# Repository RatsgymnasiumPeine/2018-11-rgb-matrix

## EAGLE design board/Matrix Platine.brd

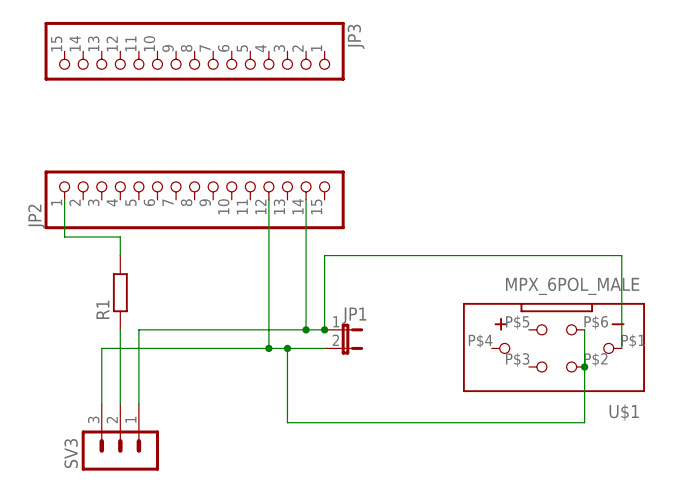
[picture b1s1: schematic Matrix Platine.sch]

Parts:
JP1: JP1E; JP1
JP2, JP3: PINHD-1X15; 1X15
R1: R-EU_0204/7; 0204/7
SV3: MA03-1
U$1: MPX_6POL_MALE; MPX_MALE

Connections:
unnamed: JP2.1, R1.2
unnamed: JP1.1, JP2.14, SV3.1, U$1.P$1 (1)
unnamed: JP1.2, JP2.12, SV3.3, U$1.P$2 (2), U$1.P$6 (6)
unnamed: R1.1, SV3.2

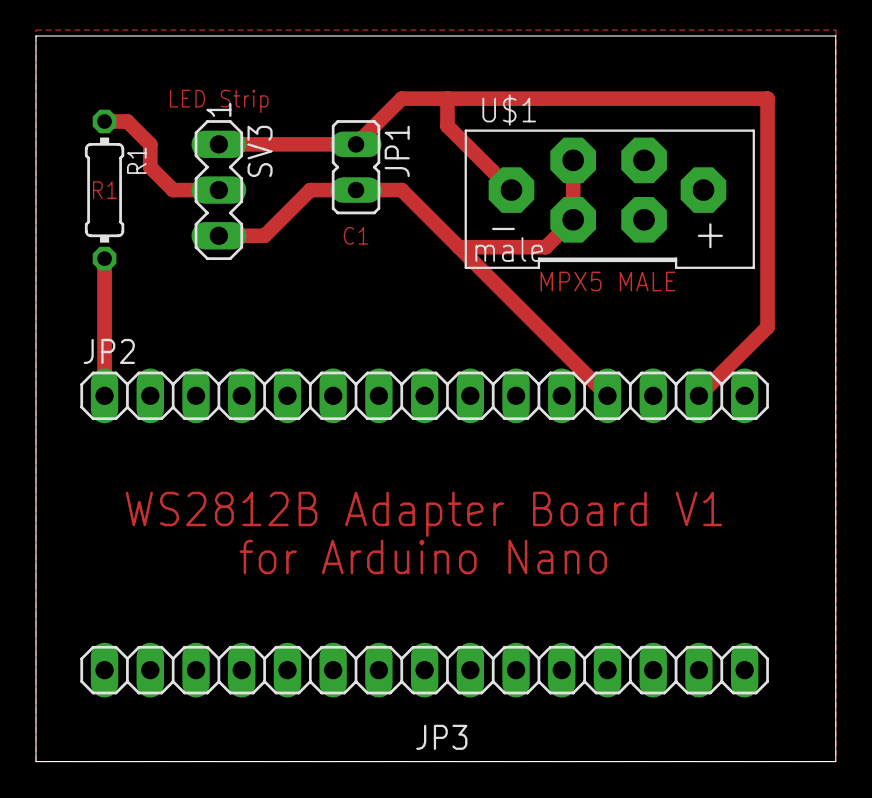
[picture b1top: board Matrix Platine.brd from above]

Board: 2 copper layers, 44.4 x 40.3 mm, 6 parts (0 on the bottom side), 4 nets.

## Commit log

2018-11-05 Init
